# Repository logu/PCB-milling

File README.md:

# PCB-milling

PCB milling can be seen as printing a circuit on to a piece of copper. This allows us to
check our design before having it Professionally made.

The milling is done on a copper substrate, it is a piece of fiber glass which has one side or both side covered in copper. The copper layers are what form the traces after being put through the milling machine.

The main purpuse here is to test different end mills and settings to get a decent result in PCB milling

## CNC Router

A CNC router is a computer-controlled cutting machine related to the hand held router used for cutting various hard materials, such as wood, composites, aluminium, steel, plastics, and foams. CNC stands for computer numerical control.
Here the following CNC router is tested for the PCB milling process.

This CNC router is from [CNC Shop](http://www.cnc-shop.ch/cnc3040.html)

* Model: 3040 v3.0
* Weight: 40kg
* Materiel: Casted aluminium
* Spindle speed: 6000 - 24000 tr/min
* Spindle power: 800W
* Collet fixture: ER11

Dimensions |  X  |  Y  |  Z  |
-----------|-----|-----|-----|
Travel size| 300 | 400 |  50
Table siez | 320 | 580 |  85

## Milling bits

Milling cutters are cutting tools typically used in milling machines or machining centers to perform milling operations They remove material by their movement within the machine or directly from the cutter's shape. The milling bits are fixed to the spindle by usinf ER 11 collet.
Tool Shank Diameter : 3 mm

### Trace cutout bits (Endmill)

Precision endmills are used to cut out the copper so that traces
are formed on the copper conductor.

* Solid Carbide V-Shaped Engraving Tool Bit

Included angle | Tip width | Price | Suplier
---------------|:----------|:------|:-----
       10°     |    0.1    | 5 bits for 6,50 € |[Amazon](https://www.amazon.fr/gp/product/B00D3GU558/ref=oh_aui_detailpage_o03_s00?ie=UTF8&psc=1) |
       15°     |    0.1    | 1 bit for 13,50 € |[Iron wood](http://www.ironwood-distribution.com/stylets_diametre_3/stylet_d3_angle_15%C2%B0/stylet-ve-diametre-a15-e0-10-p-3842.html) |
       45°     |    0.1    | 10 bits for 1 € |[Ebay](https://www.ebay.com/itm/1-5-10PCS-Carbure-Gravure-CNC-PCB-45-0-1mm-Fraise-Foret-Couteau-Plat-3-17MM/322578275122?ssPageName=STRK%3AMEBIDX%3AIT&var=511564367365&_trksid=p2057872.m2749.l2649) |
       10°     |    0.2    | 1 bit for 4.99 € |[Ebay](https://www.ebay.com/itm/%C3%98-3x10-X-0-2mm-type-V-Burins-de-GRAVURE-pour-cnc-machine-Graveur/391434920942?ssPageName=STRK%3AMEBIDX%3AIT&_trksid=p2057872.m2749.l2649) |
       15°     |    0.2    | 1 bit for 13,50 € |[Iron wood](http://www.ironwood-distribution.com/stylets_diametre_3/stylet_d3_angle_15%C2%B0/stylet-ve-diametre-a15-e0-10-p-3842.html) |

* Tough Tip Engraving Tool

Flute | Included angle | Tip width | Price | Suplier
:-----|:---------------|:----------|:------|:-----
 1    |       25°      |    0.2    | 1 bit for 9,60 € |[CNC Fraises](https://www.cncfraises.fr/pointes-javelots-1-dent-evo/237-pointe-javelot-1-dent-25-degres-gravure-circuit-imprime.html) |

* Other interesting engraving tips

http://www.2linc.com/engraving_tools_tough_tip.htm
http://www.2linc.com/engraving_tools_composite.htm

### Drill bits

Used to drill holes for through hole parts and mouting holes.

* Micro drill bits

D      | L1     | A     |  Price | Suplier
-------|:-------|:------|:-------|:--------
0.6 mm |7.0 mm  |  130° |3,40 €  |[Iron wood](http://www.ironwood-distribution.com/outils_fraisage/micros_forets/micro-foret-60-17-hss-p-3165.html) |
0.7 mm |10.5 mm |  130° |3,40 €  |[Iron wood](http://www.ironwood-distribution.com/outils_fraisage/micros_forets/micro-foret-70-17-hss-p-3167.html)
0.8 mm |10.5 mm |  130° |3,40 €  |[Iron wood](http://www.ironwood-distribution.com/outils_fraisage/micros_forets/micro-foret-80-17-hss-p-3169.html)
1.0 mm |10.5 mm |  130° |3,40 €  |[Iron wood](http://www.ironwood-distribution.com/outils_fraisage/micros_forets/micro-foret-17-hss-p-3173.html)
1.2 mm |10.5 mm |  130° |3,40 €  |[Iron wood](http://www.ironwood-distribution.com/outils_fraisage/micros_forets/micro-foret-20-17-hss-p-3177.html)
1.5 mm |10.5 mm |  130° |3 €     |[Iron wood](http://www.ironwood-distribution.com/outils_fraisage/micros_forets/micro-foret-50-17-hss-p-3181.html)
3.0 mm |10.5 mm |  130° |3 €     |[Iron wood](http://www.ironwood-distribution.com/outils_fraisage/micros_forets/micro-foret-00-17-hss-p-3196.html)

### Routing cut-out bit

Used to cut out pcb once milling is finished

* Titanium Coat Carbide

D                |  Price | Suplier
-----------------|:-------|:-----------
0.6 mm to 1,5 mm |3,40 €  |[Amazon](https://www.amazon.fr/gp/product/B00OPY6R6I/ref=oh_aui_detailpage_o02_s00?ie=UTF8&psc=1) |

## Softwares

* CNC : Mach3
* Eagle CAD
* [pcb-gcode](http://pcbgcode.org/list.php?12)

## Tutorials

* [sparkfun](https://learn.sparkfun.com/tutorials/using-eagle-schematic)
* [Instructable](http://www.instructables.com/id/Make-your-own-PCBs-on-an-inexpensive-desktop-CNC-m/)

## Supplier

* [Ironwood](http://www.ironwood-distribution.com/outils_fraisage-c-20.html)
* [CNC Frainses](https://www.cncfraises.fr/)
* [2linc](http://www.2linc.com/)

## What Not To Do
* Don't drop the bits. They will break.
* Don't crash the tool. I know you're going to crash the tool because you don't know what you're doing, so remember not to crash the tool and you'll feel bad when you crash the tool and probably won't do it again. Just raise the spindle before you go crazy hitting return to zero and if you stop a program don't just restart it somewhere in the middle and expect everything to be OK.
* Don't forget to wear eye protection. The CNC machine is a robot that cuts things and it's not sophisticated enough to follow Asimov's laws about not hurling bits of metal into your eye.
* Don't start and stop the PC with the spindle turned on. That thing is just hooked up to a pin on the parallel port and that pin gets mercilessly diddled by legacy windows upnp probing which may surprise and/or hurt you by running the spindle. Just turn it off.
* Don't leave the mill running unattended. You need to be there to hit the pretty red e-stop button when something horrible happens.
* Don't leave a mess for the next person.

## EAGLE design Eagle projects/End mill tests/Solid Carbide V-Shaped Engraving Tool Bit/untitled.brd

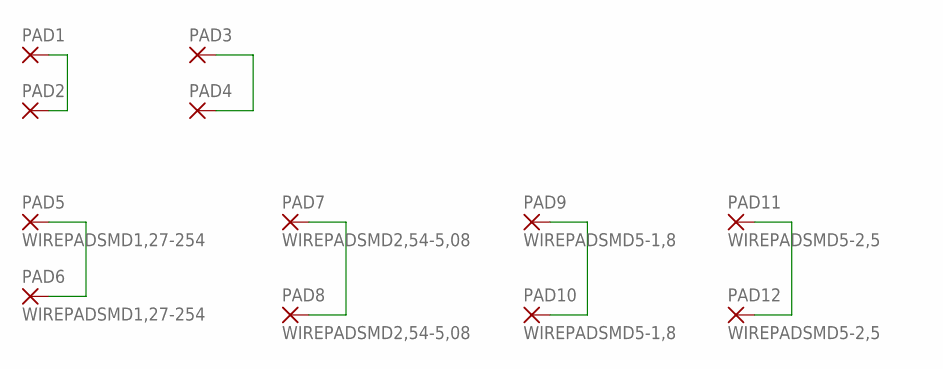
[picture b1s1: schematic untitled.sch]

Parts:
PAD1, PAD2: SMD2; SMD1,27-2,54
PAD3, PAD4: SMD5; SMD2,54-5,08
PAD5, PAD6: WIREPADSMD1,27-254; SMD1,27-2,54
PAD7, PAD8: WIREPADSMD2,54-5,08; SMD2,54-5,08
PAD9, PAD10: WIREPADSMD5-1,8; 5-1,8
PAD11, PAD12: WIREPADSMD5-2,5; 5-2,5

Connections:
unnamed: PAD1.1, PAD2.1
unnamed: PAD3.1, PAD4.1
unnamed: PAD5.1, PAD6.1
unnamed: PAD7.1, PAD8.1
unnamed: PAD9.1, PAD10.1
unnamed: PAD11.1, PAD12.1

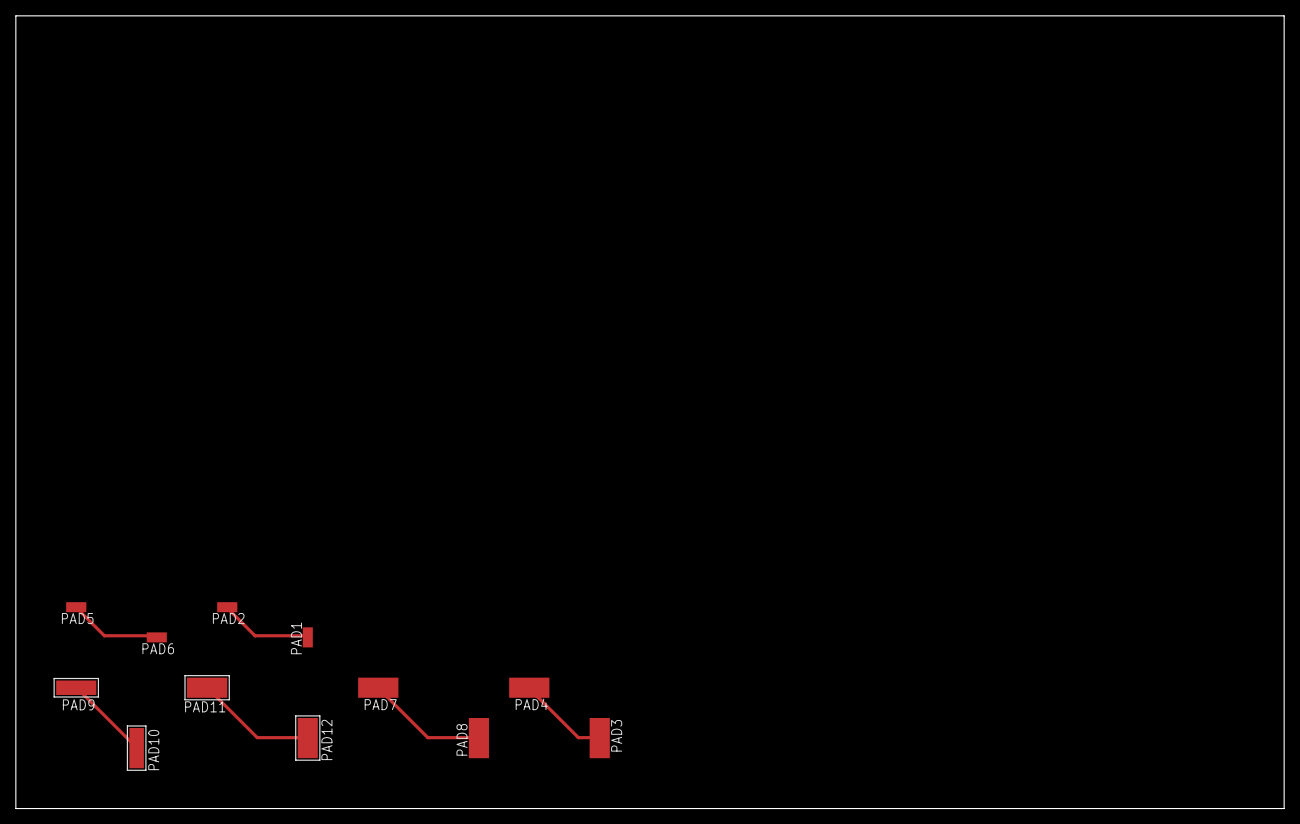
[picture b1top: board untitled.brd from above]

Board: 2 copper layers, 160.0 x 100.0 mm, 12 parts (0 on the bottom side), 6 nets.

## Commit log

2018-01-17 Added definition and typo check
2018-01-21 added eagle prjoect and test MD files
